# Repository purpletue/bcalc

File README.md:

# BCALC
A calculator designed specifically for people with visual impairment, fully FOSS so anybody can make it.
# THIS PROJECT DOES NOT CURRENTLY HAVE FIRMWARE AND IS A WIP. IF SOMEBODY WANTS TO HELP WITH IT, PLEASE HELP ME I SUCK AT C++
## What is this, anyway?
BCalc is a calculator meant for people who have difficulty seeing. it uses a rotary encoder for input and vibration combined with Morse code for output.

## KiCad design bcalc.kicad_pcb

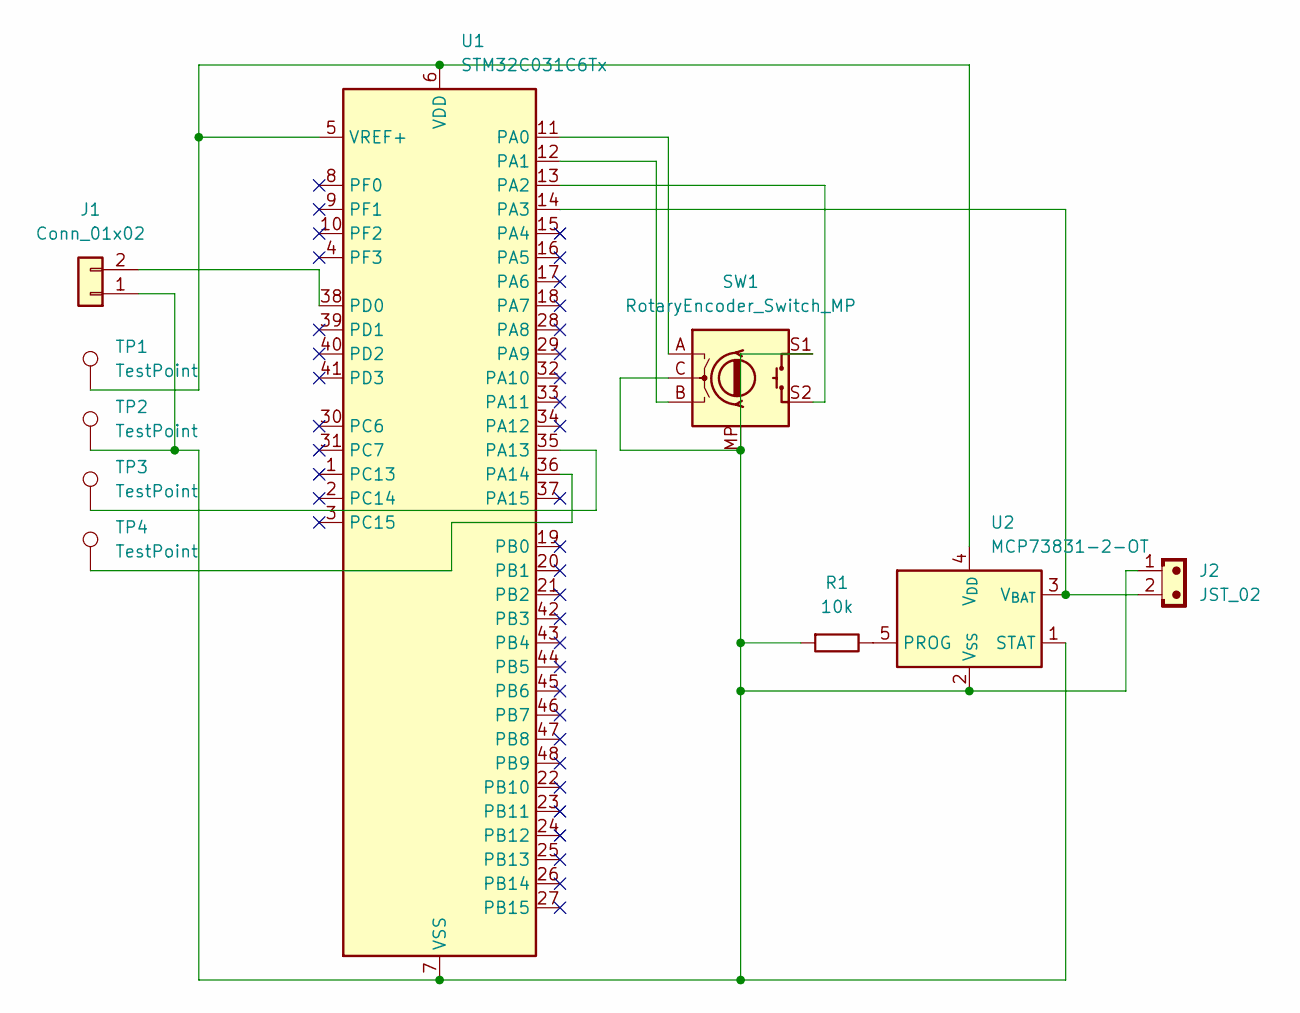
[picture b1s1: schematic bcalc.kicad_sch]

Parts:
J1: Conn_01x02; PinHeader_1x02_P1.00mm_Vertical
J2: JST_02; JST_EH_B2B-EH-A_1x02_P2.50mm_Vertical
R1: 10k; R_01005_0402Metric
SW1: RotaryEncoder_Switch_MP; RotaryEncoder_Alps_EC11E-Switch_Vertical_H20mm
TP1, TP2, TP3, TP4: TestPoint; Pin_D1.0mm_L10.0mm
U1: STM32C031C6Tx; LQFP-48_7x7mm_P0.5mm
U2: MCP73831-2-OT; SOT-23-5

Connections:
unnamed: J1.1, J2.1, R1.1, SW1.C, SW1.MP, SW1.S1, TP2.1 (1_1), U1.7 (VSS), U2.1 (STAT), U2.2 (V_{SS})
unnamed: J1.2, U1.38 (PD0)
unnamed: SW1.A, U1.11 (PA0)
unnamed: SW1.B, U1.12 (PA1)
unnamed: SW1.S2, U1.13 (PA2)
unnamed: J2.2, U1.14 (PA3), U2.3 (V_{BAT})
unnamed: TP3.1 (1_1), U1.35 (PA13)
unnamed: TP4.1 (1_1), U1.36 (PA14)
unnamed: TP1.1 (1_1), U1.5 (VREF+), U1.6 (VDD), U2.4 (V_{DD})
unnamed: R1.2, U2.5 (PROG)

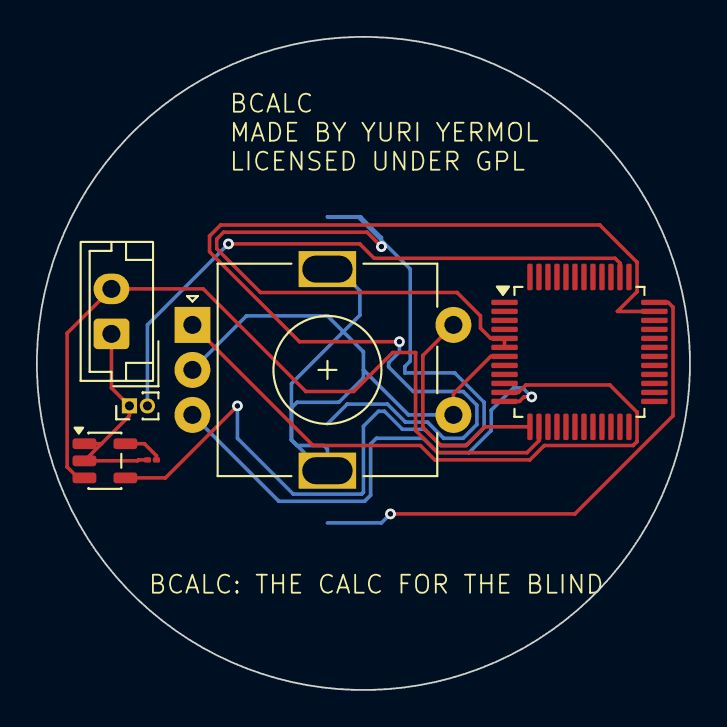
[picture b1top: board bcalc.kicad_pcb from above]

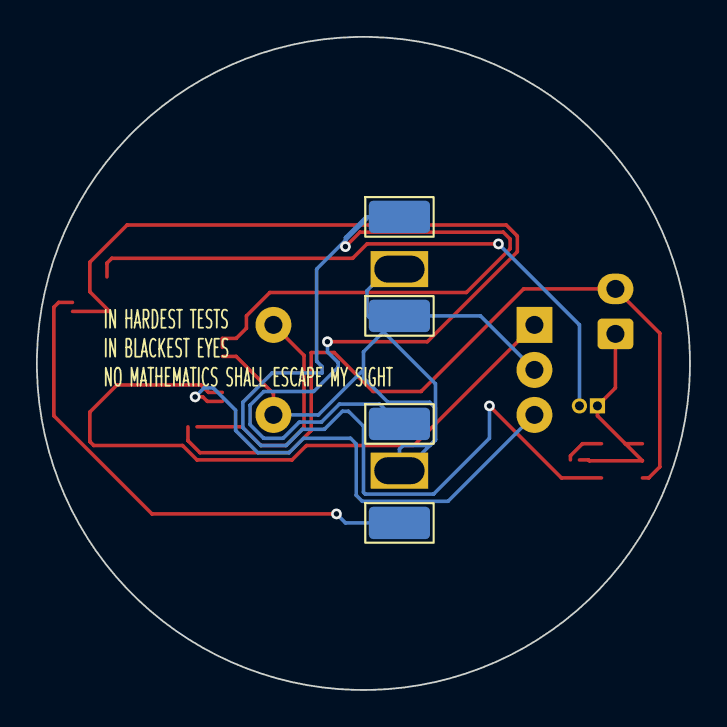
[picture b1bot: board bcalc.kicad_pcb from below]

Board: 2 copper layers, 36.3 x 36.3 mm, 10 parts (4 on the bottom side), 10 nets.

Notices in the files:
bcalc.kicad_pcb:
LICENSED UNDER GPL
